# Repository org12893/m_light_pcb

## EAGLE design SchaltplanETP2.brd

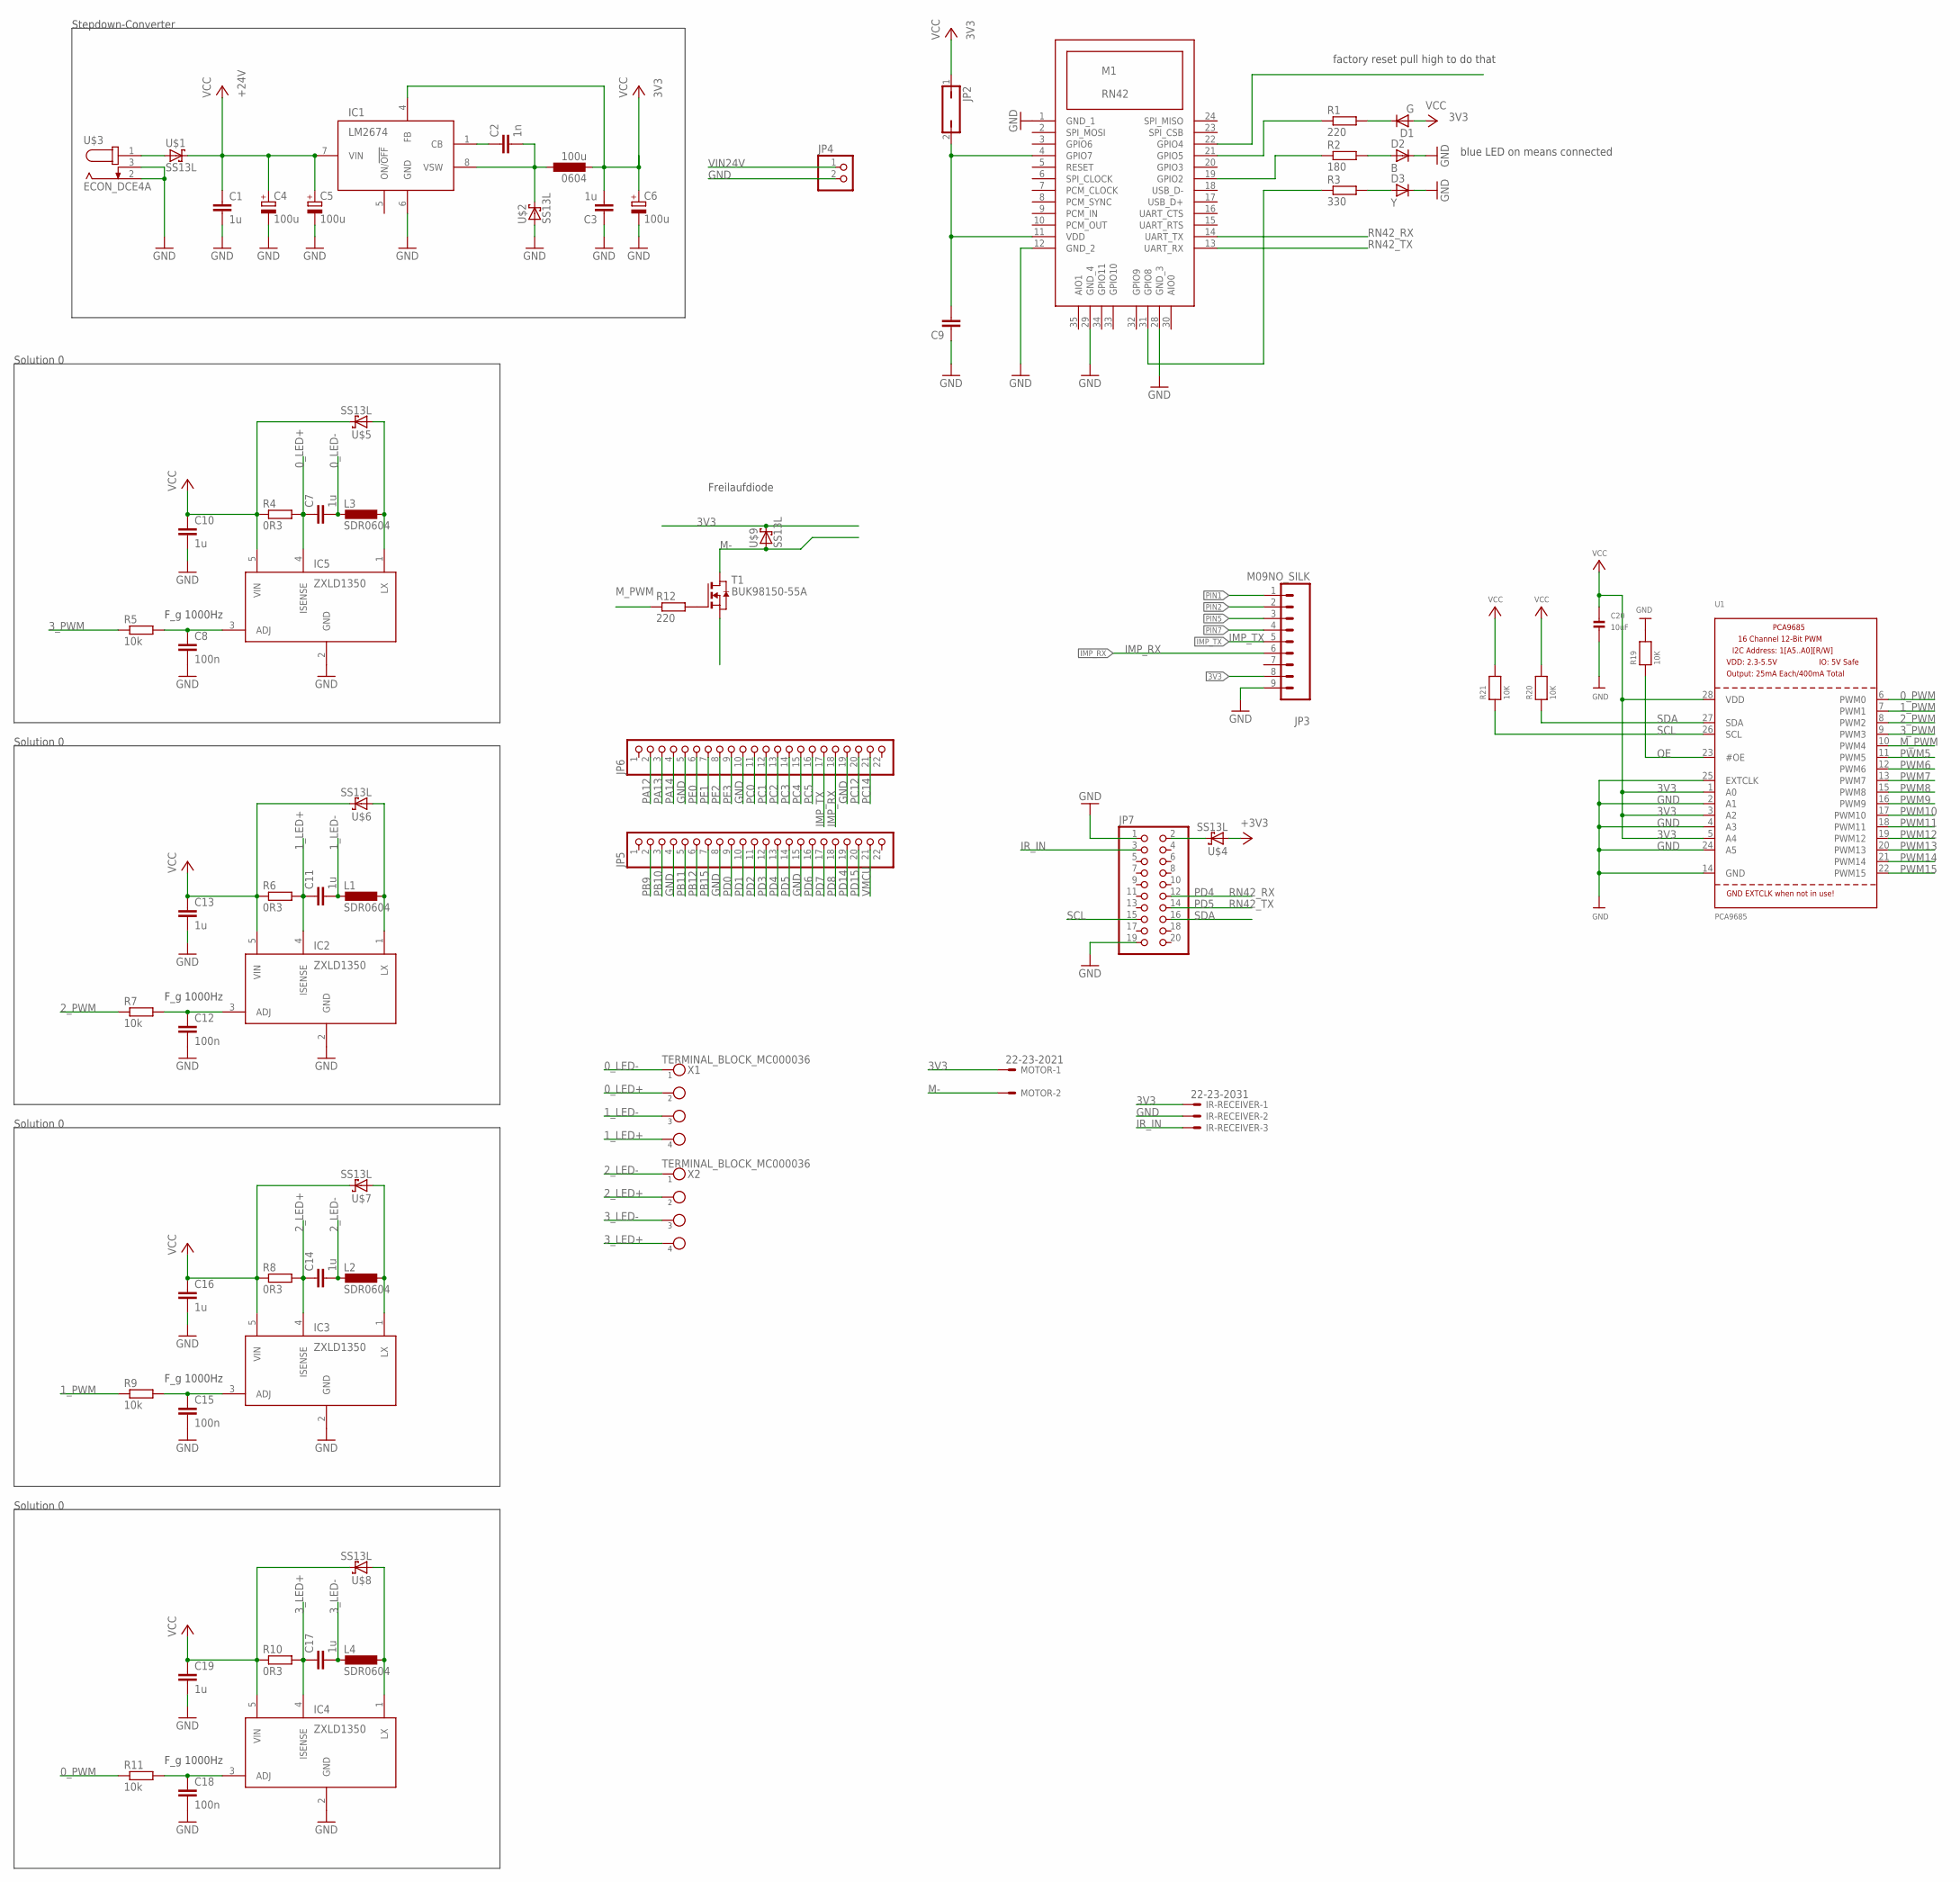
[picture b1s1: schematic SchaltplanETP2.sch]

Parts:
0604: 100u; SDR0604
C1, C3: 1u; C050-025X075
C2: 1n; C0805
C4, C5, C6: 100u; E2,5-7
C7, C10, C11, C13, C14, C16, C17, C19: 1u; C050-024X044
C8, C12, C15, C18: 100n; C0805
C9: C-EUC1808; C1808
C20: 10uF; 0805
D1: G; D0805
D2: B; D0805
D3: Y; D0805
IC1: LM2674; SO08
IC2, IC3, IC4, IC5: ZXLD1350; TSOT23-5L
IR-RECEIVER: 22-23-2031
JP2: JP1Q; JP1
JP3: M09NO_SILK; 1X09_NO_SILK
JP4: PINHD-1X2; 1X02
JP5, JP6: PINHD-1X22; 1X22
JP7: PINHD-2X10; 2X10
L1, L2, L3, L4: SDR0604
M1: RN42_BLUETOOTH
MOTOR: 22-23-2021
R1: 220; R0603
R2: 180; R0603
R3: 330; R0603
R4, R6, R8, R10: 0R3; M0805
R5, R7, R9, R11: 10k; M0805
R12: 220; M0805
R19, R20, R21: 10K; 0805
T1: BUK98150-55A; SOT223
U1: PCA9685; TSSOP28
U$1, U$2, U$4, U$5, U$6, U$7, U$8, U$9: SS13L; SUB-SMA
U$3: ECON_DCE4A; DC_JACK_ECON_DCE4A
X1, X2: TERMINAL_BLOCK_MC000036

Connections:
0_LED+: C7.1, IC5.4 (ISENSE), R4.2, X1.2
0_LED-: C7.2, L3.2, X1.1
0_PWM: R11.1, U1.6 (PWM0)
1_LED+: C11.1, IC2.4 (ISENSE), R6.2, X1.4
1_LED-: C11.2, L1.2, X1.3
1_PWM: R9.1, U1.7 (PWM1)
2_LED+: C14.1, IC3.4 (ISENSE), R8.2, X2.2
2_LED-: C14.2, L2.2, X2.1
2_PWM: R7.1, U1.8 (PWM2)
3V3: 0604.2, C3.2, C6.+, C20.1, D1.A, IC1.4 (FB), IR-RECEIVER.1, JP2.1, JP3.8, MOTOR.1, R20.2, R21.2, U1.1 (A0), U1.3 (A2), U1.5 (A4), U1.28 (VDD), U$4.A, U$9.C
3_LED+: C17.1, IC4.4 (ISENSE), R10.2, X2.4
3_LED-: C17.2, L4.2, X2.3
3_PWM: R5.1, U1.9 (PWM3)
+24V: C1.1, C4.+, C5.+, C10.1, C13.1, C16.1, C19.1, IC1.7 (VIN), IC2.5 (VIN), IC3.5 (VIN), IC4.5 (VIN), IC5.5 (VIN), R4.1, R6.1, R8.1, R10.1, U$1.C, U$5.C, U$6.C, U$7.C, U$8.C
GND: C1.2, C3.1, C4.-, C5.-, C6.-, C8.2, C9.1, C10.2, C12.2, C13.2, C15.2, C16.2, C18.2, C19.2, C20.2, D2.C, D3.C, IC1.6 (GND), IC2.2 (GND), IC3.2 (GND), IC4.2 (GND), IC5.2 (GND), IR-RECEIVER.2, JP3.9, JP4.2, JP5.4, JP5.8, JP7.1, JP7.19, M1.1 (GND_1), M1.12 (GND_2), M1.28 (GND_3), M1.29 (GND_4), R19.2, U1.2 (A1), U1.4 (A3), U1.14 (GND), U1.24 (A5), U1.25 (EXTCLK), U$2.A, U$3.2, U$3.3
IMP_RX: JP3.6, JP6.18
IMP_TX: JP3.5, JP6.17
IR_IN: IR-RECEIVER.3, JP7.3
M-: MOTOR.2, T1.2 (D), T1.4 (D), U$9.A
M_PWM: R12.1, U1.10 (PWM4)
unnamed: R12.2, T1.1 (G)
unnamed: C2.1, IC1.1 (CB)
unnamed: 0604.1, C2.2, IC1.8 (VSW), U$2.C
unnamed: JP7.2, U$4.C
unnamed: C9.2, JP2.2, M1.4 (GPIO7), M1.11 (VDD)
unnamed: IC5.1 (LX), L3.1, U$5.A
unnamed: D1.C, R1.2
unnamed: D2.A, R2.2
unnamed: D3.A, R3.2
unnamed: M1.21 (GPIO5), R1.1
unnamed: M1.19 (GPIO2), R2.1
unnamed: M1.31 (GPIO8), R3.1
unnamed: C8.1, IC5.3 (ADJ), R5.2
unnamed: IC2.1 (LX), L1.1, U$6.A
unnamed: C12.1, IC2.3 (ADJ), R7.2
unnamed: IC3.1 (LX), L2.1, U$7.A
unnamed: C15.1, IC3.3 (ADJ), R9.2
unnamed: IC4.1 (LX), L4.1, U$8.A
unnamed: C18.1, IC4.3 (ADJ), R11.2
OE: R19.1, U1.23 (#OE)
PA12: JP6.2
PA13: JP6.3
PB9: JP5.2
PB10: JP5.3
PB11: JP5.5
PB12: JP5.6
PB15: JP5.7
PIN1: JP3.1
PIN2: JP3.2
PIN5: JP3.3
PIN7: JP3.4
PWM5: U1.11 (PWM5)
PWM6: U1.12 (PWM6)
PWM7: U1.13 (PWM7)
PWM8: U1.15 (PWM8)
PWM9: U1.16 (PWM9)
PWM10: U1.17 (PWM10)
PWM11: U1.18 (PWM11)
PWM12: U1.19 (PWM12)
PWM13: U1.20 (PWM13)
PWM14: U1.21 (PWM14)
PWM15: U1.22 (PWM15)
RN42_RX: JP7.12, M1.14 (UART_TX)
RN42_TX: JP7.14, M1.13 (UART_RX)
SCL: JP7.15, R21.1, U1.26 (SCL)
SDA: JP7.16, R20.1, U1.27 (SDA)
VIN24V: JP4.1, U$1.A, U$3.1

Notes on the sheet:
Stepdown-Converter
PD5
PD4
Solution 0
F_g 1000Hz
blue LED on means connected
factory reset pull high to do that
Freilaufdiode

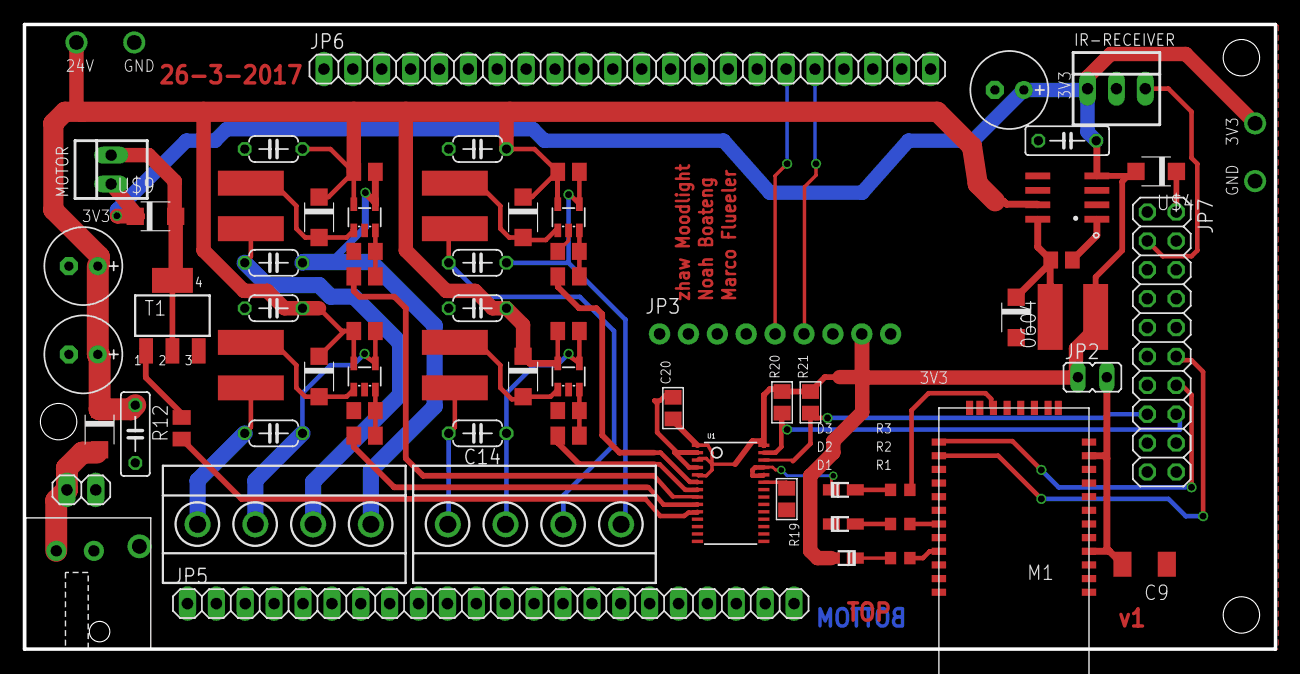
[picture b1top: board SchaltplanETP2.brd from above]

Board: 2 copper layers, 110.0 x 54.9 mm, 70 parts (0 on the bottom side), 45 nets.

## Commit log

2017-03-07 added gitignore file
2017-03-07 added first version of pcb and circuit
2017-03-18 Changed LED of pin 21 from the RN42 module to fit the datasheet. Added Jumpber behind DC-Jack to allow direct soldering of cables. Added Terminal Blocks for LEDs.
    Placed part onto grid.
2017-03-19 added terminal header and connection
2017-03-20 connected leds directly to 24V
2017-03-20 rearranged driver 1 and 2
2017-03-20 placed driver 3 and 4
2017-03-23 added diode to motor additional pinheader for screw terminal
2017-03-23 added placed screw terminal and diode for motor driver
2017-03-23 added PCA9685 i2c to pwm 16 channel driver
2017-03-26 rearrangement of the components
2017-03-26 changes added polygon and some changes for version1

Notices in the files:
parts and their libraries:
SparkFun-Connectors: Licensing: CC v3.0 Share-Alike You are welcome to use this library for commercial purposes.
